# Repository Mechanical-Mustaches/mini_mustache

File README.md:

Temporary home for a browser based serial terminal can be found here https://anfroholic.github.io/stache-terminal/

We are the Mechanical Mustaches
FIRST® Robotics Team 8122

this is Mo the mini_mustache robotic car

Mo Dance for the FIRST Time!

Mo designed by our very own Olivia

Coming soon! Carl the Controller

here is a race put on by our amazing lead progammer Angie!!

Still in development but some previews are:

Mo hosts webpages to edit himself
## Homepage

## Live coding REPL like code terminal

## Stachboard
Dashboard is autopopulated with motors, servos, agents and many other inputs and outputs that are created

## Mo also has an editor where you can edit your own code

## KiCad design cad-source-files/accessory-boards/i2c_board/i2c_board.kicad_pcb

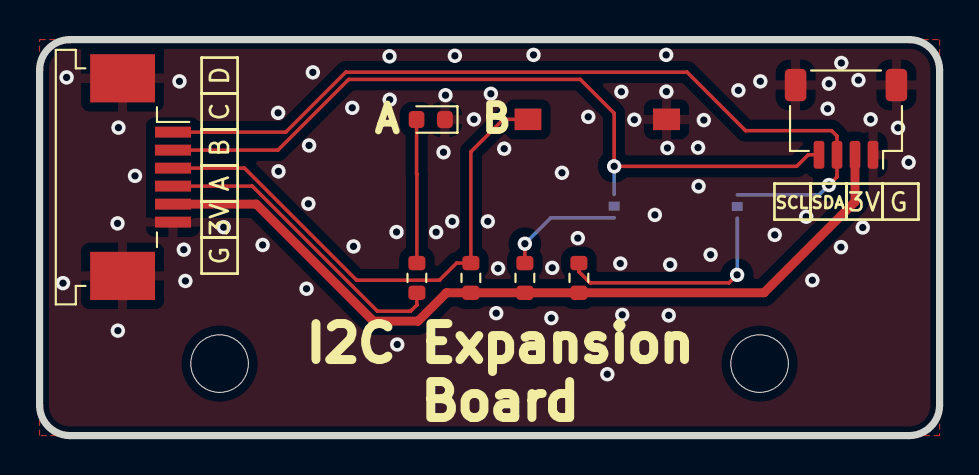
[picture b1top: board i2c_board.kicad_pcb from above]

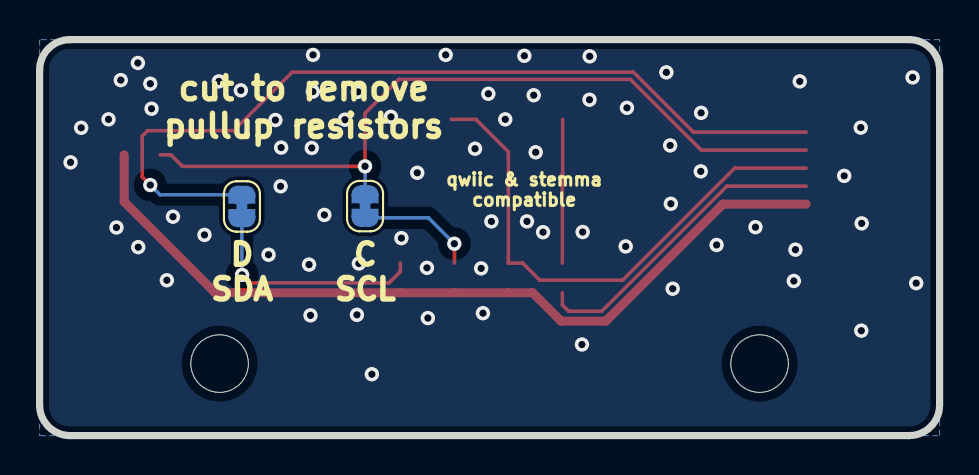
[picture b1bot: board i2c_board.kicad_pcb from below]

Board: 2 copper layers, 50.0 x 22.0 mm, 12 parts (2 on the bottom side), 9 nets.

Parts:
D1: led_g; LED_0603_1608Metric
H1, H2: MountingHole; MountingHole_3.2mm_M3_ISO14580
J1: Conn_01x04_MountingPin; JST_SH_SM04B-SRSS-TB_1x04-1MP_P1.00mm_Horizontal
J9: Conn_01x06_MountingPin; TE_84952-6_1x06-1MP_P1.0mm_Horizontal
JP1, JP2: Jumper_2_Open; SolderJumper-2_P1.3mm_Bridged_RoundedPad1.0x1.5mm
R1, R4: 10k; R_0603_1608Metric
R2, R3: 4.7k; R_0603_1608Metric
SW1: SW_Push; SWITCH_2x3_SMD_TACTILE_GREEN

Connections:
+3V3: J1.2, J9.5, R1.2, R2.2, R3.2
/A: J9.4, R4.1
/B: J9.3, R1.1, SW1.1
/C: J1.4, J9.2, JP1.1 (A)
/D: J1.3, J9.1, JP2.1 (A)
GND: D1.1 (K), J1.1, J1.MP (MountPin), J9.6, J9.MP (MountPin), SW1.2
unnamed: D1.2 (A), R4.2
unnamed: JP1.2 (B), R2.1
unnamed: JP2.2 (B), R3.1

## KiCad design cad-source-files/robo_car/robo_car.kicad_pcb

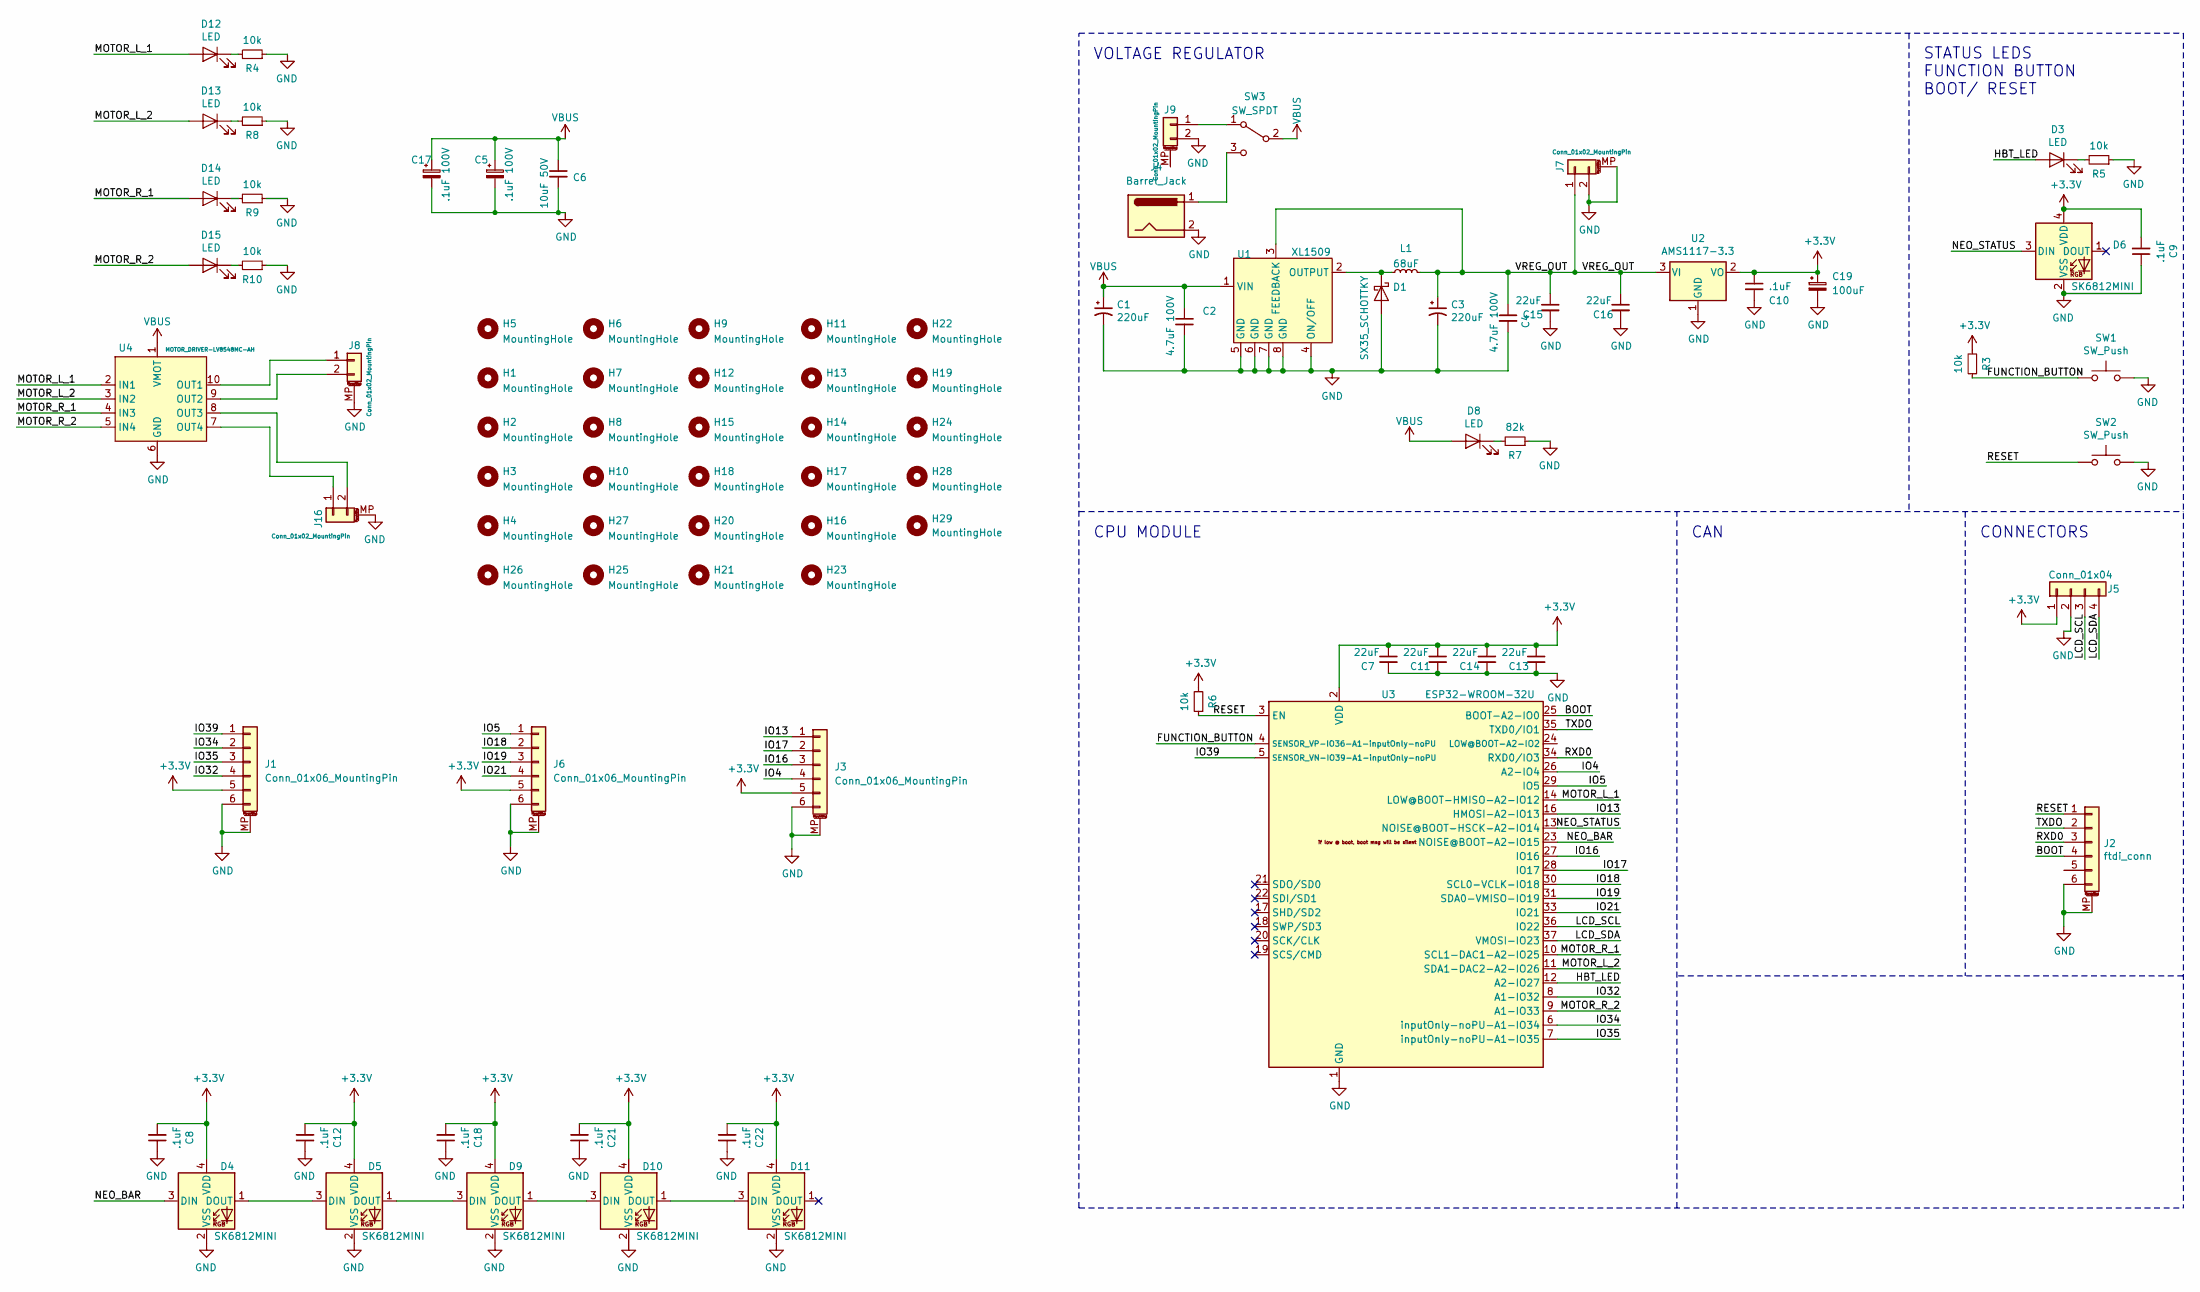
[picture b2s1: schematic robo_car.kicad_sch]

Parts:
C1, C3: 220uF; CP_Elec_10x10.5
C2, C4: 4.7uF 100V; C_0805_2012Metric
C5, C17: .1uF 100V; C_0805_2012Metric
C6: 10uF 50V; C_1206_3216Metric
C7, C11, C13, C14, C15, C16: 22uF; C_0805_2012Metric
C8, C9, C10, C12, C18, C21, C22: .1uF; C_0603_1608Metric
C19: 100uF; CP_EIA-3528-21_Kemet-B
D1: SX35_SCHOTTKY; D_SMA
D3, D8, D12, D13, D14, D15: LED; LED_0603_1608Metric
D4, D5, D6, D9, D10, D11: SK6812MINI; LED_SK6812MINI_PLCC4_3.5x3.5mm_P1.75mm
H1, H2, H3, H4, H5, H6, H7, H8, H9, H10, H11, H12, H13, H14, H15, H16, H17, H18, H19, H20, H25, H26, H27, H28, H29: MountingHole; MountingHole_3.2mm_M3_ISO14580
H21, H22, H23, H24: MountingHole; MountingHole_2.7mm_M2.5_ISO14580
J1, J3, J6: Conn_01x06_MountingPin; TE_84952-6_1x06-1MP_P1.0mm_Horizontal
J2: ftdi_conn; JST_SH_SM06B-SRSS-TB_1x06-1MP_P1.00mm_Horizontal
J4: Barrel_Jack; BarrelJack_Horizontal
J5: Conn_01x04; PinSocket_1x04_P2.54mm_Vertical
J7: Conn_01x02_MountingPin; JST_PH_B2B-PH-K_1x02_P2.00mm_Vertical
J8, J16: Conn_01x02_MountingPin; JST_PH_S2B-PH-K_1x02_P2.00mm_Horizontal
J9: Conn_01x02_MountingPin; JST_XH_B2B-XH-AM_1x02_P2.50mm_Vertical
L1: 68uF; INDUCTOR-68uH
R3, R4, R5, R6, R8, R9, R10: 10k; R_0603_1608Metric
R7: 82k; R_0603_1608Metric
SW1, SW2: SW_Push; SWITCH_2x3_SMD_TACTILE_GREEN
SW3: SW_SPDT; SW_SLIDE_SS-12D10L9
U1: XL1509; SOIC-8_3.9x4.9mm_P1.27mm
U2: AMS1117-3.3; SOT-223-3_TabPin2
U3: ESP32-WROOM-32U; ESP32-WROOM-32U_evezor
U4: MOTOR_DRIVER-LV8548MC-AH; SOIC-10_LV8548MC-AH_evezor

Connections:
+3V3: C7.1, C8.2, C9.2, C10.1, C11.1, C12.2, C13.1, C14.1, C18.2, C19.1, C21.2, C22.2, D4.4 (VDD), D5.4 (VDD), D6.4 (VDD), D9.4 (VDD), D10.4 (VDD), D11.4 (VDD), J1.5, J3.5, J5.1, J6.5, R3.2, R6.2, U2.2 (VO), U3.2 (VDD); also elsewhere on the board
/BOOT: J2.4, U3.25 (BOOT-A2-IO0)
/FUNCTION_BUTTON: R3.1, SW1.1, U3.4 (SENSOR_VP-IO36-A1-inputOnly-noPU)
/HBT_LED: D3.2 (A), U3.12 (A2-IO27)
/IO4: J3.4, U3.26 (A2-IO4)
/IO5: J6.1, U3.29 (IO5)
/IO13: J3.1, U3.16 (HMOSI-A2-IO13)
/IO16: J3.3, U3.27 (IO16)
/IO17: J3.2, U3.28 (IO17)
/IO18: J6.2, U3.30 (SCL0-VCLK-IO18)
/IO19: J6.3, U3.31 (SDA0-VMISO-IO19)
/IO21: J6.4, U3.33 (IO21)
/IO32: J1.4, U3.8 (A1-IO32)
/IO34: J1.2, U3.6 (inputOnly-noPU-A1-IO34)
/IO35: J1.3, U3.7 (inputOnly-noPU-A1-IO35)
/IO39: J1.1, U3.5 (SENSOR_VN-IO39-A1-inputOnly-noPU)
/LCD_SCL: J5.3, U3.36 (IO22)
/LCD_SDA: J5.4, U3.37 (VMOSI-IO23)
/MOTOR_L_1: D12.2 (A), U3.14 (LOW@BOOT-HMISO-A2-IO12), U4.2 (IN1)
/MOTOR_L_2: D13.2 (A), U3.11 (SDA1-DAC2-A2-IO26), U4.3 (IN2)
/MOTOR_R_1: D14.2 (A), U3.10 (SCL1-DAC1-A2-IO25), U4.4 (IN3)
/MOTOR_R_2: D15.2 (A), U3.9 (A1-IO33), U4.5 (IN4)
/NEO_BAR: D4.3 (DIN), U3.23 (NOISE@BOOT-A2-IO15)
/NEO_STATUS: D6.3 (DIN), U3.13 (NOISE@BOOT-HSCK-A2-IO14)
/RESET: J2.1, R6.1, SW2.1, U3.3 (EN)
/RXD0: J2.3, U3.34 (RXD0/IO3)
/TXDO: J2.2, U3.35 (TXD0/IO1)
/VREG_OUT: C3.1, C4.1, C15.1, C16.1, J7.1, L1.1, U1.3 (FEEDBACK), U2.3 (VI)
GND: C1.2, C2.2, C3.2, C4.2, C5.2, C6.2, C7.2, C8.1, C9.1, C10.2, C11.2, C12.1, C13.2, C14.2, C15.2, C16.2, C17.2, C18.1, C19.2, C21.1, C22.1, D1.2 (A), D4.2 (VSS), D5.2 (VSS), D6.2 (VSS), D9.2 (VSS), D10.2 (VSS), D11.2 (VSS), J1.6, J1.MP (MountPin), J2.6, J2.MP (MountPin), J3.6, J3.MP (MountPin), J4.2, J5.2, J6.6, J6.MP (MountPin), J7.2, J7.MP (MountPin), J8.MP (MountPin), J9.2, J16.MP (MountPin), R4.1, R5.1, R7.1, R8.1, R9.1, R10.1, SW1.2, SW2.2, U1.4 (ON/OFF), U1.5 (GND), U1.6 (GND), U1.7 (GND), U1.8 (GND), U2.1 (GND), U3.1 (GND), U3.15 (GND), U3.38 (GND), U3.39 (GND), U4.6 (GND); also elsewhere on the board
unnamed: D1.1 (K), L1.2, U1.2 (OUTPUT)
unnamed: D3.1 (K), R5.2
unnamed: D4.1 (DOUT), D5.3 (DIN)
unnamed: D5.1 (DOUT), D9.3 (DIN)
unnamed: D8.1 (K), R7.2
unnamed: D10.1 (DOUT), D11.3 (DIN)
unnamed: D9.1 (DOUT), D10.3 (DIN)
unnamed: D12.1 (K), R4.2
unnamed: D13.1 (K), R8.2
unnamed: D14.1 (K), R9.2
unnamed: D15.1 (K), R10.2
unnamed: J4.1, SW3.3 (C)
unnamed: J8.1, U4.10 (OUT1)
unnamed: J8.2, U4.9 (OUT2)
unnamed: J16.1, U4.7 (OUT4)
unnamed: J16.2, U4.8 (OUT3)
unnamed: J9.1, SW3.1 (A)
VBUS: C1.1, C2.1, C5.1, C6.1, C17.1, D8.2 (A), SW3.2 (B), U1.1 (VIN), U4.1 (VMOT)

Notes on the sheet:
VOLTAGE REGULATOR
CPU MODULE
CAN
STATUS LEDS FUNCTION BUTTON BOOT/ RESET
CONNECTORS

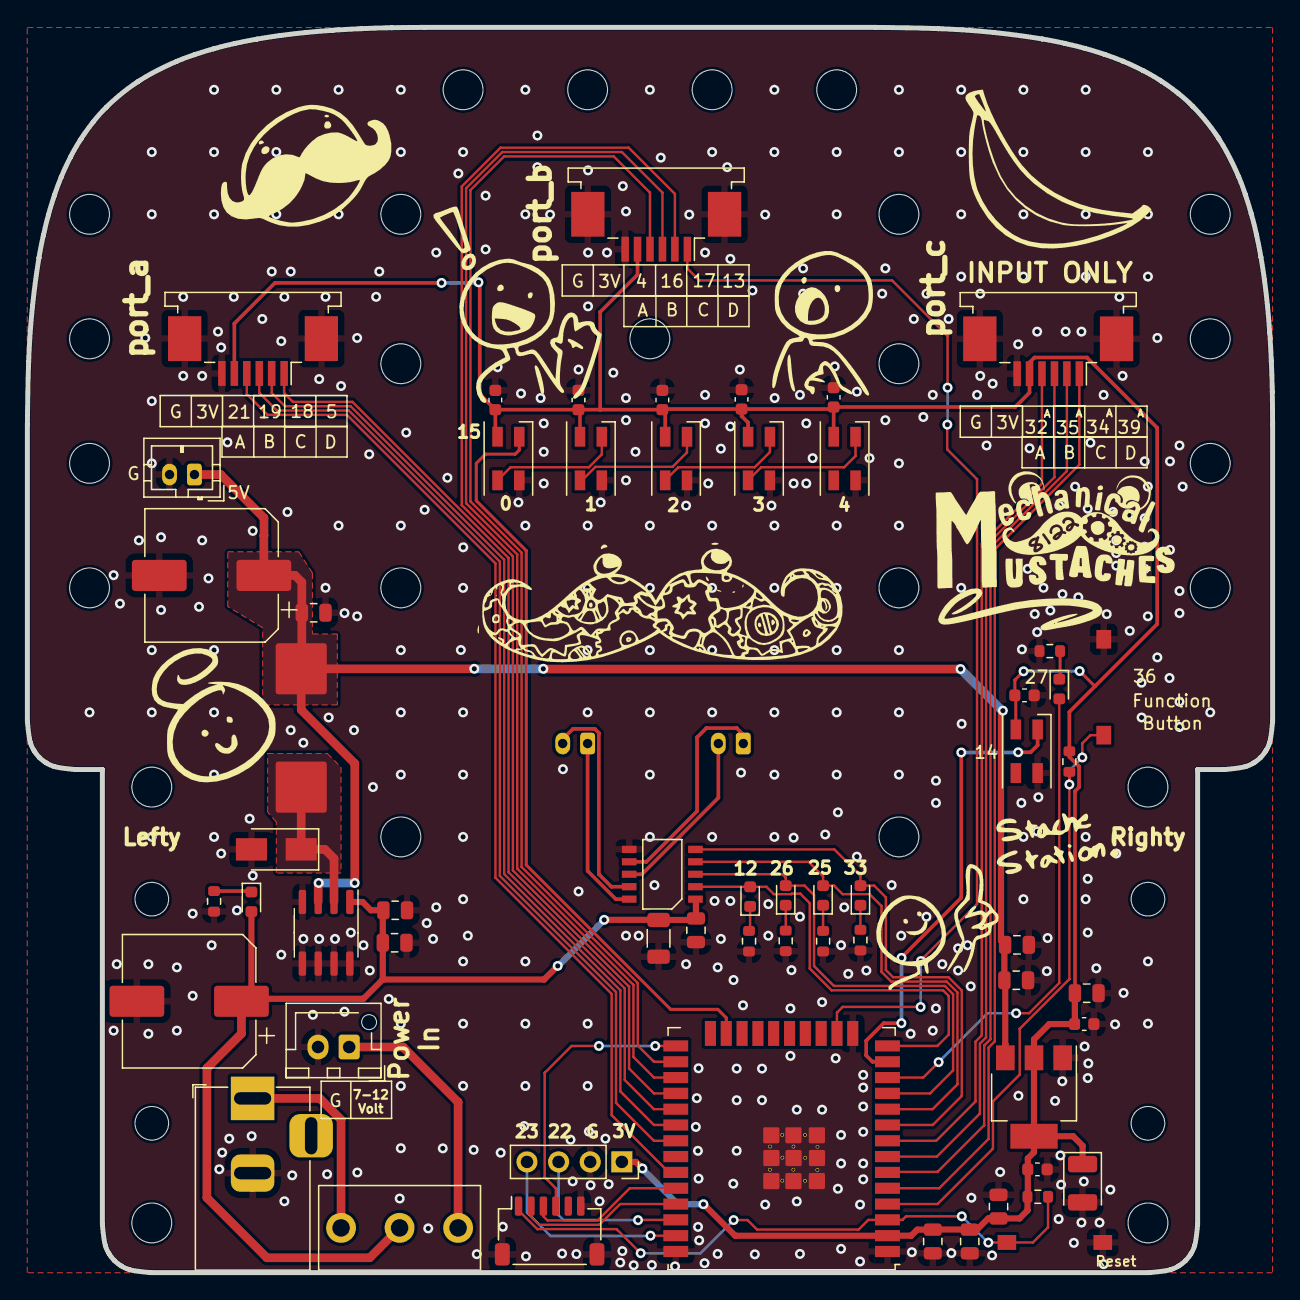
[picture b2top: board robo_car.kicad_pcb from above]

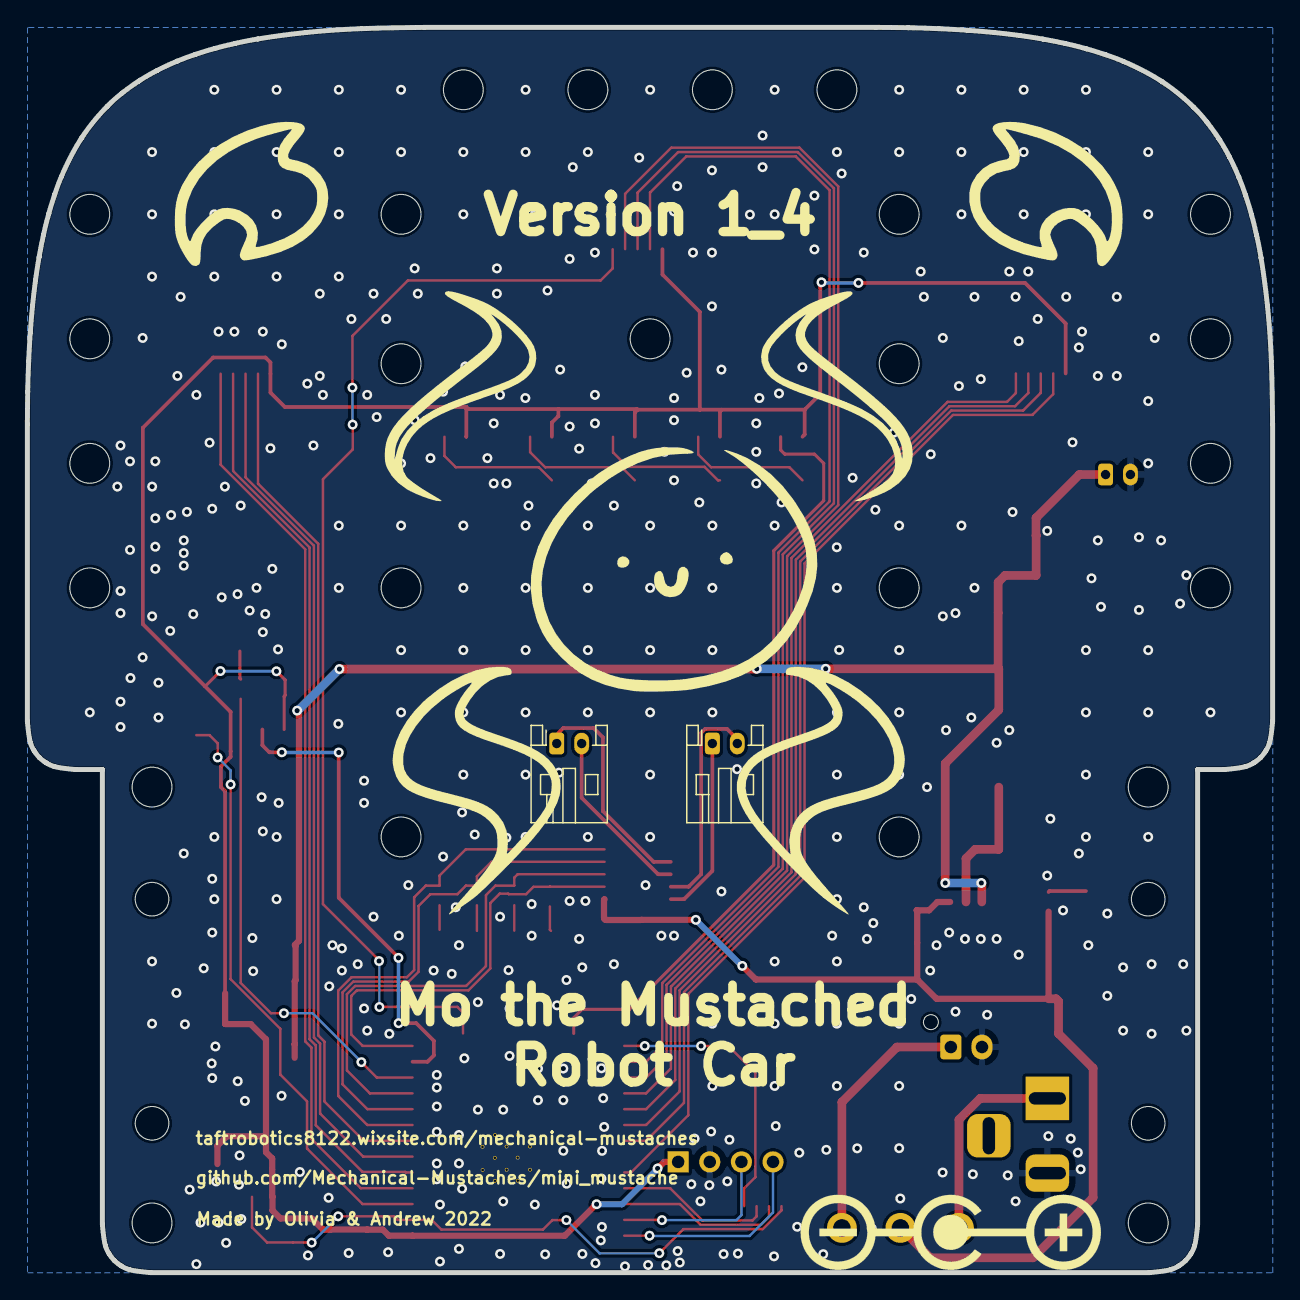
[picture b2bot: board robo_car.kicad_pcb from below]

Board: 2 copper layers, 100.0 x 100.0 mm, 90 parts (2 on the bottom side), 47 nets.

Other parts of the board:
C14#2: .1uF; C_0603_1608Metric

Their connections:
+3V3: C14#2.1; also elsewhere on the board
GND: C14#2.2; also elsewhere on the board

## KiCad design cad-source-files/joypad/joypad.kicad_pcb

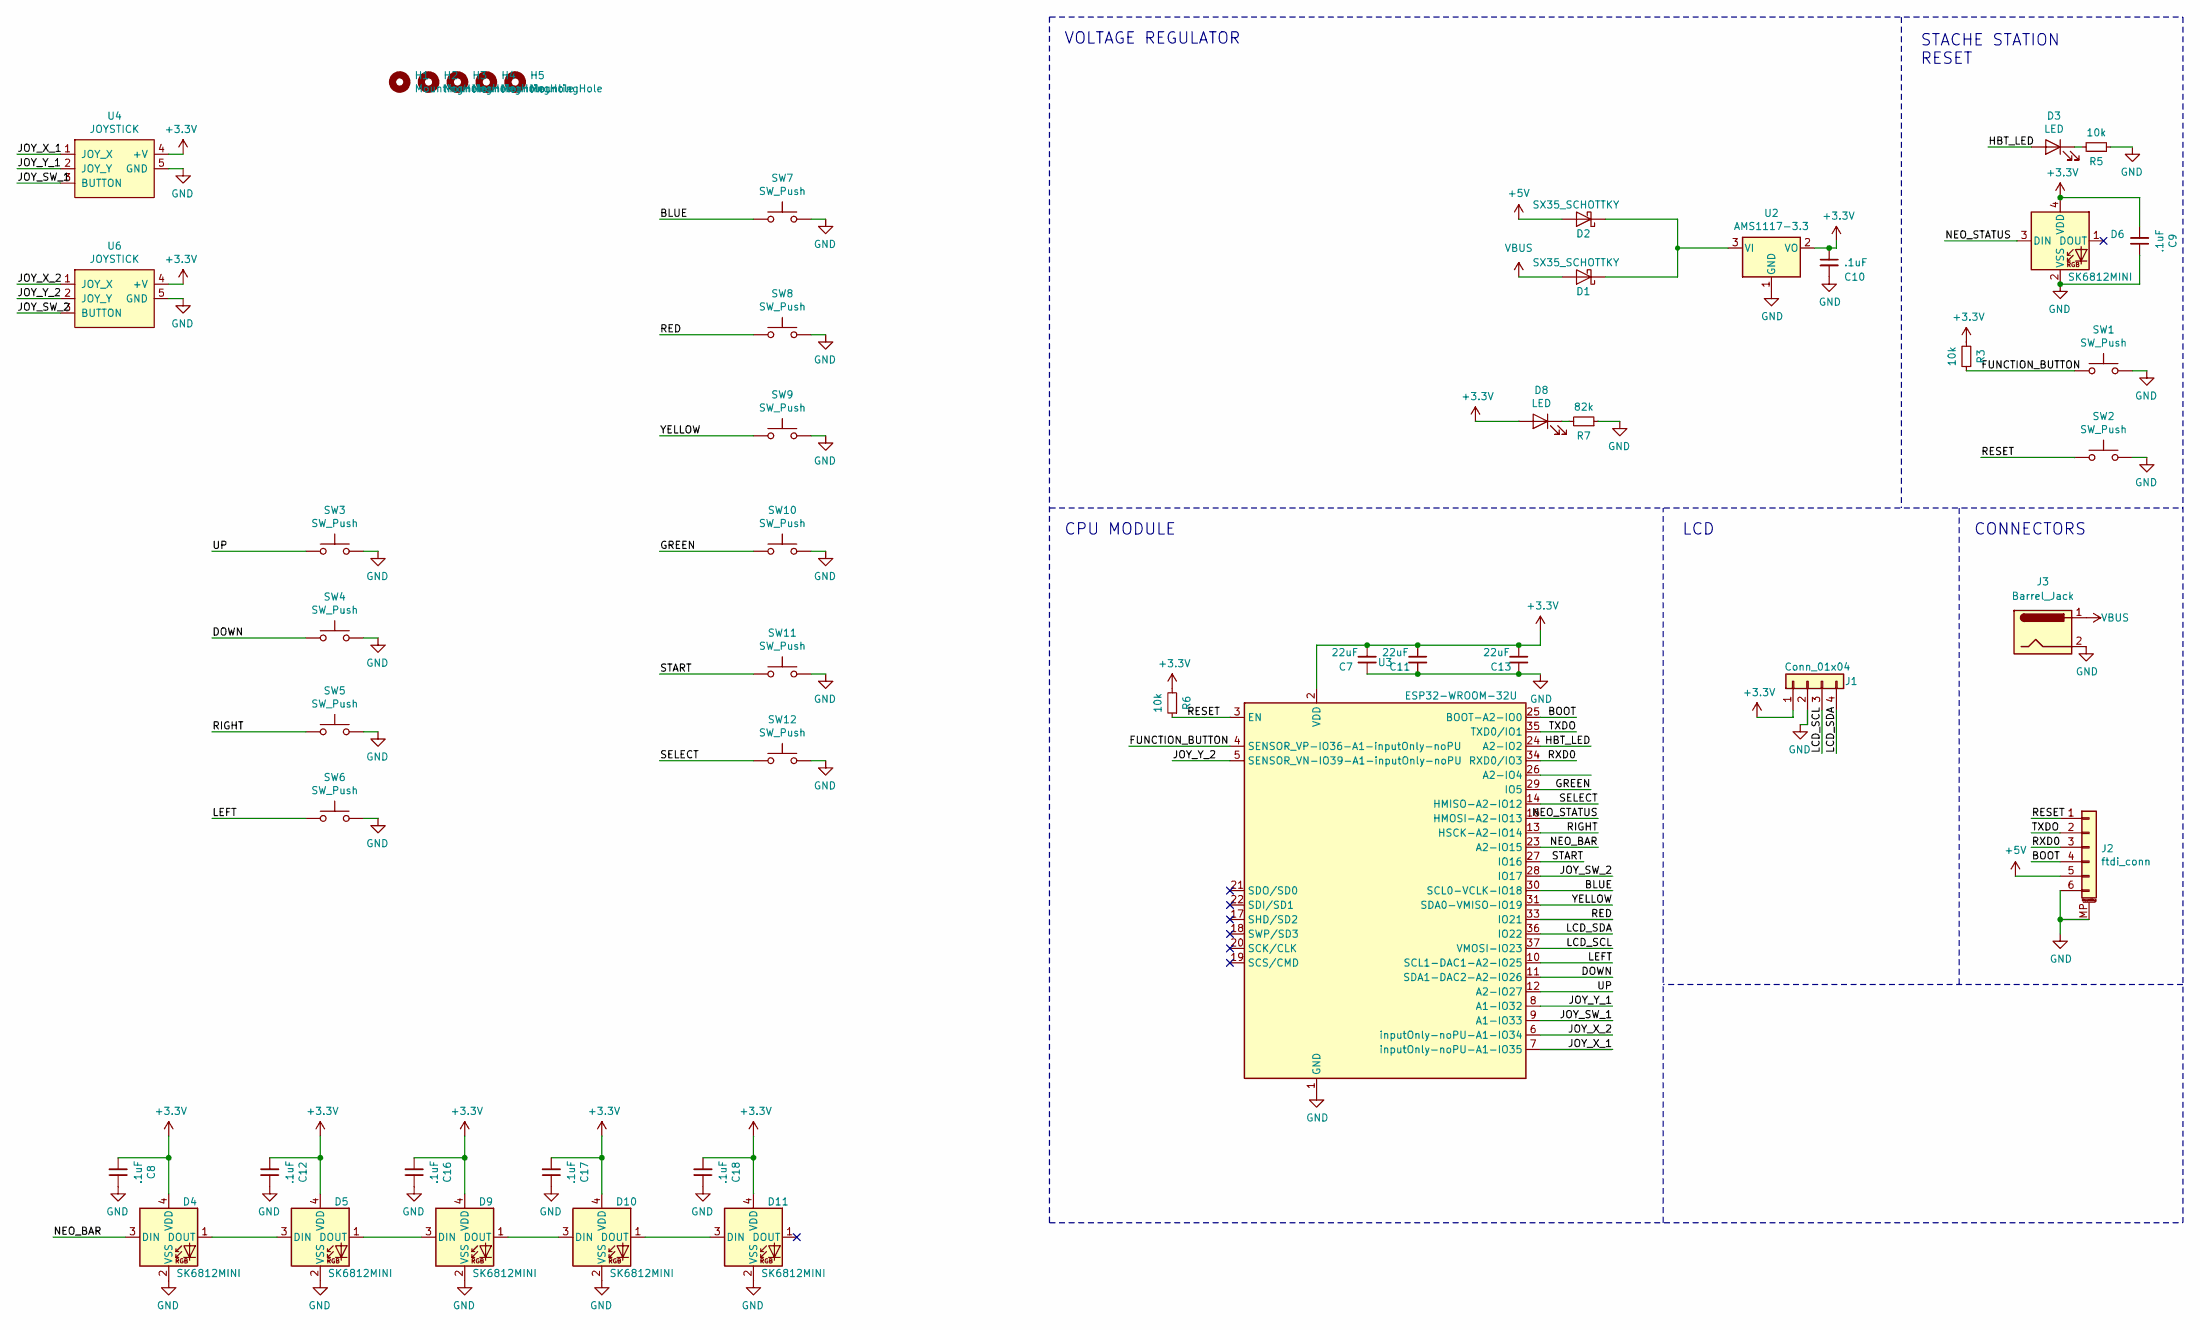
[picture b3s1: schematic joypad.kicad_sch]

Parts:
C7, C11, C13: 22uF; C_0805_2012Metric
C8, C9, C10, C12, C16, C17, C18: .1uF; C_0603_1608Metric
D1, D2: SX35_SCHOTTKY; D_SMA
D3, D8: LED; LED_0603_1608Metric
D4, D5, D6, D9, D10, D11: SK6812MINI; LED_SK6812MINI_PLCC4_3.5x3.5mm_P1.75mm
H1, H2, H3, H4, H5: MountingHole; MountingHole_2.5mm_Pad
J1: Conn_01x04; PinSocket_1x04_P2.54mm_Vertical
J2: ftdi_conn; JST_SH_SM06B-SRSS-TB_1x06-1MP_P1.00mm_Horizontal
J3: Barrel_Jack; BarrelJack_Horizontal
R3, R5, R6: 10k; R_0603_1608Metric
R7: 82k; R_0603_1608Metric
SW1, SW2, SW3, SW4, SW5, SW6, SW11, SW12: SW_Push; SWITCH_2x3_SMD_TACTILE_GREEN
SW7, SW8, SW9, SW10: SW_Push; 12mm_pushbutton
U2: AMS1117-3.3; SOT-223-3_TabPin2
U3: ESP32-WROOM-32U; ESP32-WROOM-32U_evezor
U4, U6: JOYSTICK

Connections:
+3V3: C7.1, C8.2, C9.2, C10.1, C11.1, C12.2, C13.1, C16.2, C17.2, C18.2, D4.4 (VDD), D5.4 (VDD), D6.4 (VDD), D8.2 (A), D9.4 (VDD), D10.4 (VDD), D11.4 (VDD), J1.1, R3.2, R6.2, U2.2 (VO), U3.2 (VDD), U4.4 (+V), U6.4 (+V)
+5V: D2.2 (A), J2.5
/BLUE: SW7.1, U3.30 (SCL0-VCLK-IO18)
/BOOT: J2.4, U3.25 (BOOT-A2-IO0)
/DOWN: SW4.1, U3.11 (SDA1-DAC2-A2-IO26)
/FUNCTION_BUTTON: R3.1, SW1.1, U3.4 (SENSOR_VP-IO36-A1-inputOnly-noPU)
/GREEN: SW10.1, U3.29 (IO5)
/HBT_LED: D3.2 (A), U3.24 (A2-IO2)
/JOY_SW_1: U3.9 (A1-IO33), U4.3 (BUTTON)
/JOY_SW_2: U3.28 (IO17), U6.3 (BUTTON)
/JOY_X_1: U3.7 (inputOnly-noPU-A1-IO35), U4.1 (JOY_X)
/JOY_X_2: U3.6 (inputOnly-noPU-A1-IO34), U6.1 (JOY_X)
/JOY_Y_1: U3.8 (A1-IO32), U4.2 (JOY_Y)
/JOY_Y_2: U3.5 (SENSOR_VN-IO39-A1-inputOnly-noPU), U6.2 (JOY_Y)
/LCD_SCL: J1.3, U3.37 (VMOSI-IO23)
/LCD_SDA: J1.4, U3.36 (IO22)
/LEFT: SW6.1, U3.10 (SCL1-DAC1-A2-IO25)
/NEO_BAR: D4.3 (DIN), U3.23 (A2-IO15)
/NEO_STATUS: D6.3 (DIN), U3.16 (HMOSI-A2-IO13)
/RED: SW8.1, U3.33 (IO21)
/RESET: J2.1, R6.1, SW2.1, U3.3 (EN)
/RIGHT: SW5.1, U3.13 (HSCK-A2-IO14)
/RXD0: J2.3, U3.34 (RXD0/IO3)
/SELECT: SW12.1, U3.14 (HMISO-A2-IO12)
/START: SW11.1, U3.27 (IO16)
/TXDO: J2.2, U3.35 (TXD0/IO1)
/UP: SW3.1, U3.12 (A2-IO27)
/YELLOW: SW9.1, U3.31 (SDA0-VMISO-IO19)
GND: C7.2, C8.1, C9.1, C10.2, C11.2, C12.1, C13.2, C16.1, C17.1, C18.1, D4.2 (VSS), D5.2 (VSS), D6.2 (VSS), D9.2 (VSS), D10.2 (VSS), D11.2 (VSS), J1.2, J2.6, J2.MP (MountPin), J3.2, R5.1, R7.1, SW1.2, SW2.2, SW3.2, SW4.2, SW5.2, SW6.2, SW7.2, SW8.2, SW9.2, SW10.2, SW11.2, SW12.2, U2.1 (GND), U3.1 (GND), U3.15 (GND), U3.38 (GND), U3.39 (GND), U4.5 (GND), U6.5 (GND)
unnamed: D1.1 (K), D2.1 (K), U2.3 (VI)
unnamed: D3.1 (K), R5.2
unnamed: D4.1 (DOUT), D5.3 (DIN)
unnamed: D5.1 (DOUT), D9.3 (DIN)
unnamed: D8.1 (K), R7.2
unnamed: D10.1 (DOUT), D11.3 (DIN)
unnamed: D9.1 (DOUT), D10.3 (DIN)
VBUS: D1.2 (A), J3.1

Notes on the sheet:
VOLTAGE REGULATOR
CPU MODULE
LCD
STACHE STATION RESET
CONNECTORS

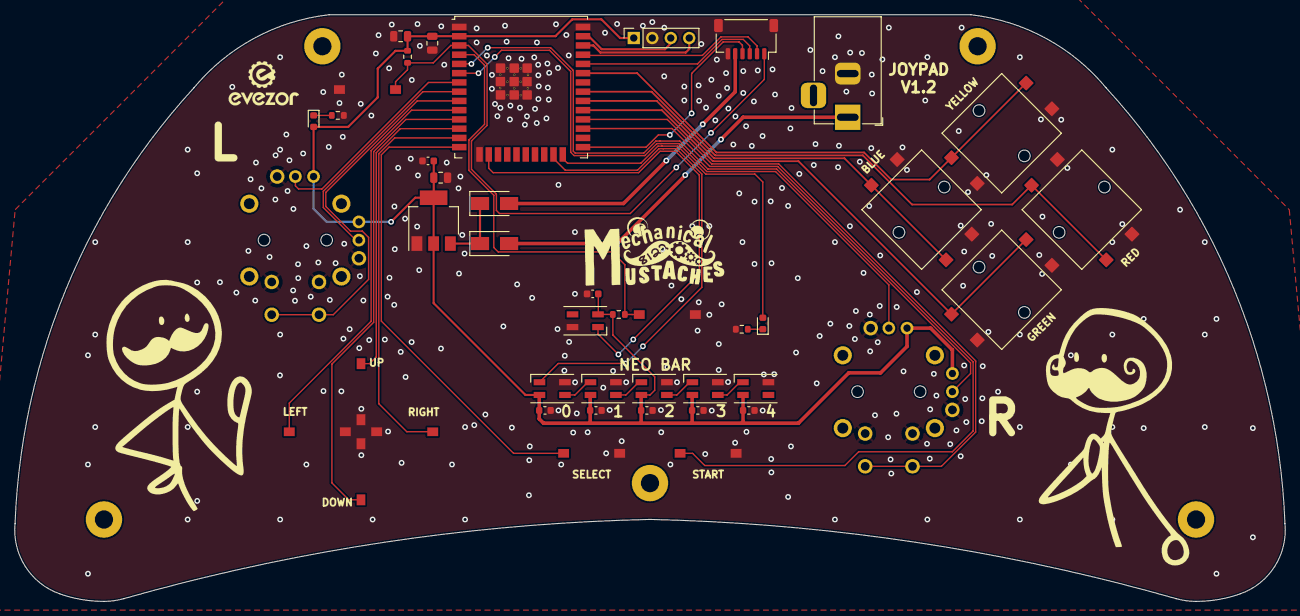
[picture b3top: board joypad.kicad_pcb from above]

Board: 2 copper layers, 174.5 x 80.6 mm, 48 parts (0 on the bottom side), 37 nets.

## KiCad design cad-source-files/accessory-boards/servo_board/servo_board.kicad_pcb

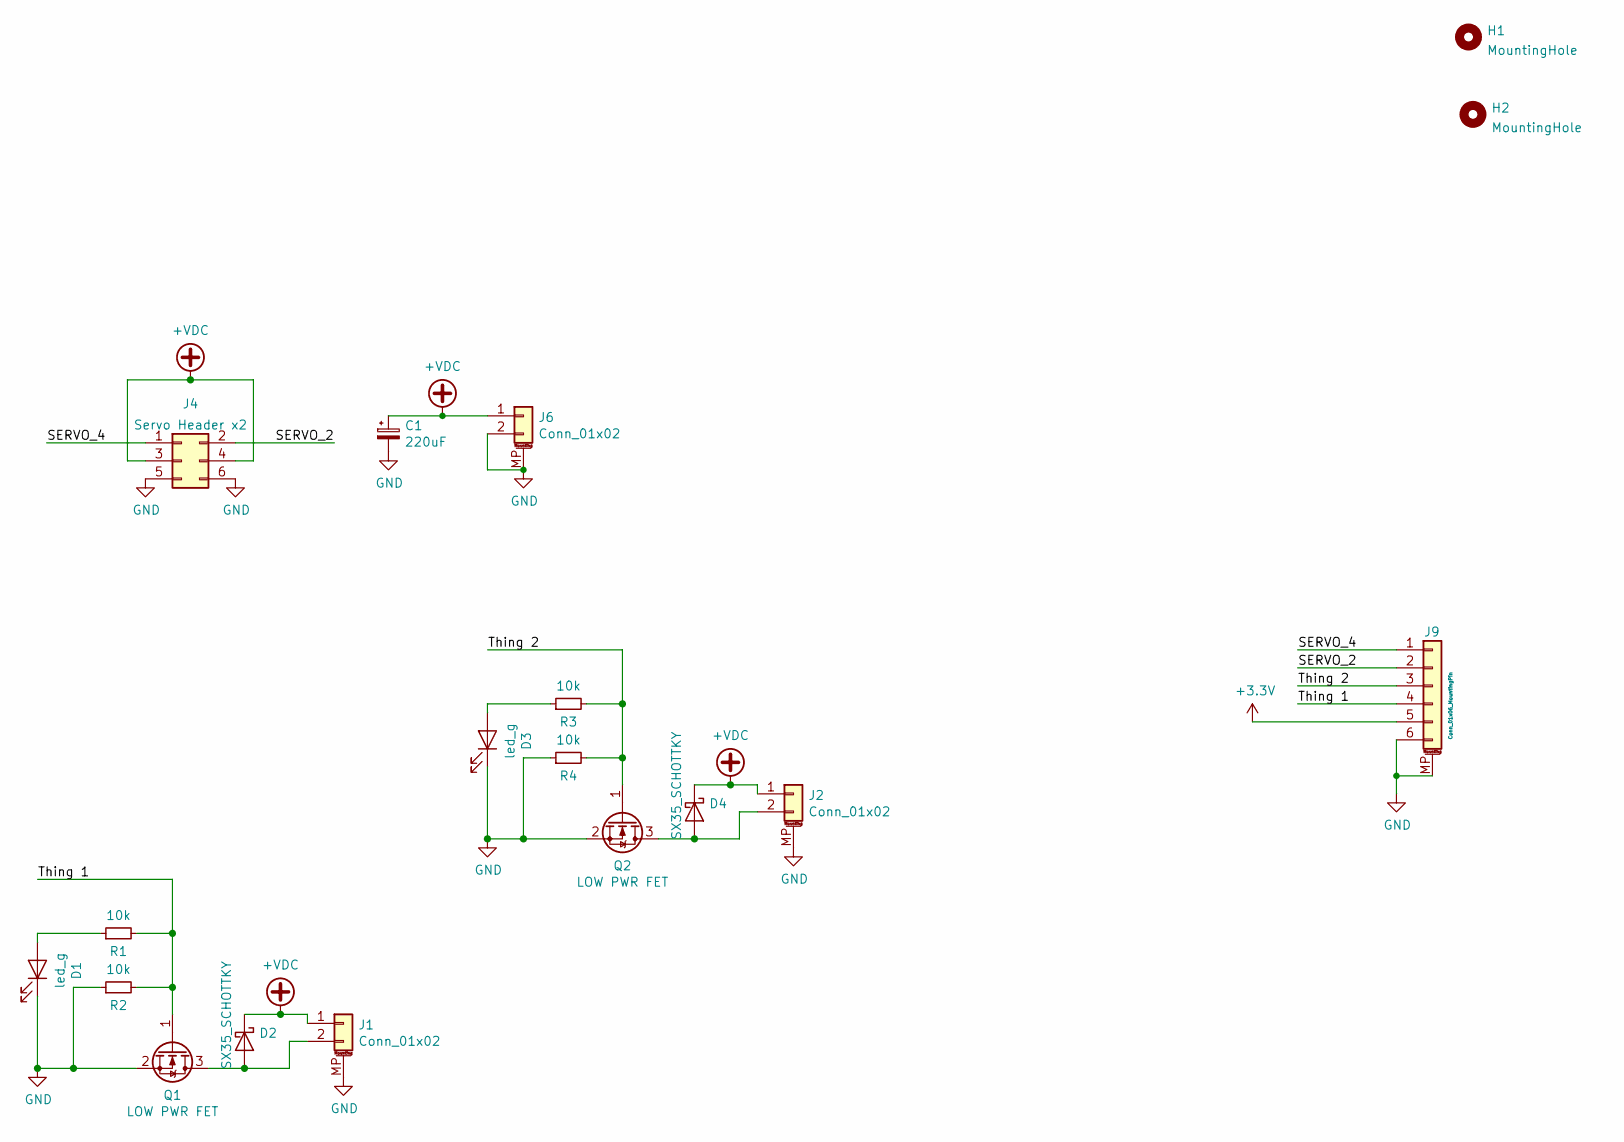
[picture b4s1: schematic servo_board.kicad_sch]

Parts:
C1: 220uF; CP_Elec_8x6.5
D1, D3: led_g; LED_0603_1608Metric
D2, D4: SX35_SCHOTTKY; D_SMA
H1, H2: MountingHole; MountingHole_3.2mm_M3_ISO14580
J1, J2, J6: Conn_01x02; JST_XH_2_VERTICAL
J4: Servo Header x2; PinHeader_2x03_P2.54mm_Vertical_SMD
J9: Conn_01x06_MountingPin; TE_84952-6_1x06-1MP_P1.0mm_Horizontal
Q1, Q2: LOW PWR FET; SOT-23
R1, R2, R3, R4: 10k; R_0603_1608Metric

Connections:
+3V3: J9.5
+VDC: C1.1, D2.1 (K), D4.1 (K), J1.1, J2.1, J4.3, J4.4, J6.1
/SERVO_2: J4.2, J9.2
/SERVO_4: J4.1, J9.1
/Thing 1: J9.4, Q1.1 (G), R1.2, R2.2
/Thing 2: J9.3, Q2.1 (G), R3.2, R4.2
GND: C1.2, D1.1 (K), D3.1 (K), J1.MP (MountPin), J2.MP (MountPin), J4.5, J4.6, J6.2, J6.MP (MountPin), J9.6, J9.MP (MountPin), Q1.2 (S), Q2.2 (S), R2.1, R4.1
unnamed: D1.2 (A), R1.1
unnamed: D2.2 (A), J1.2, Q1.3 (D)
unnamed: D3.2 (A), R3.1
unnamed: D4.2 (A), J2.2, Q2.3 (D)

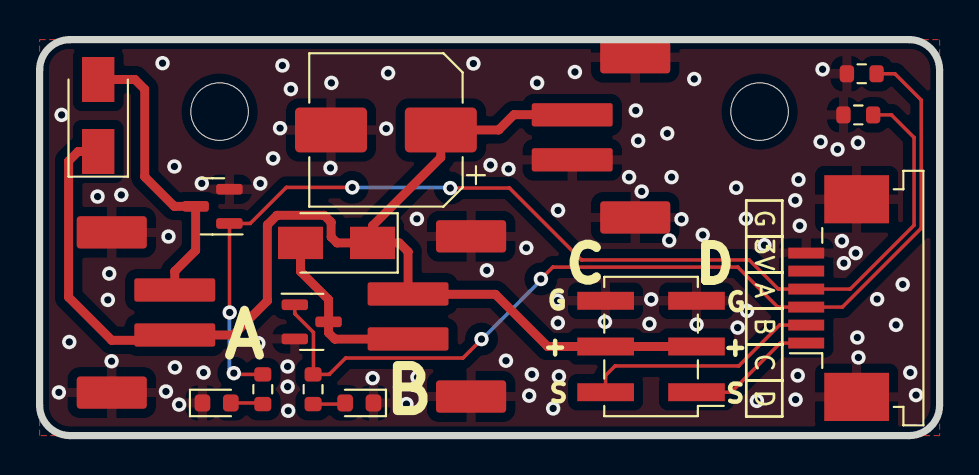
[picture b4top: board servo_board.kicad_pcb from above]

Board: 2 copper layers, 50.0 x 22.0 mm, 18 parts (0 on the bottom side), 10 nets.

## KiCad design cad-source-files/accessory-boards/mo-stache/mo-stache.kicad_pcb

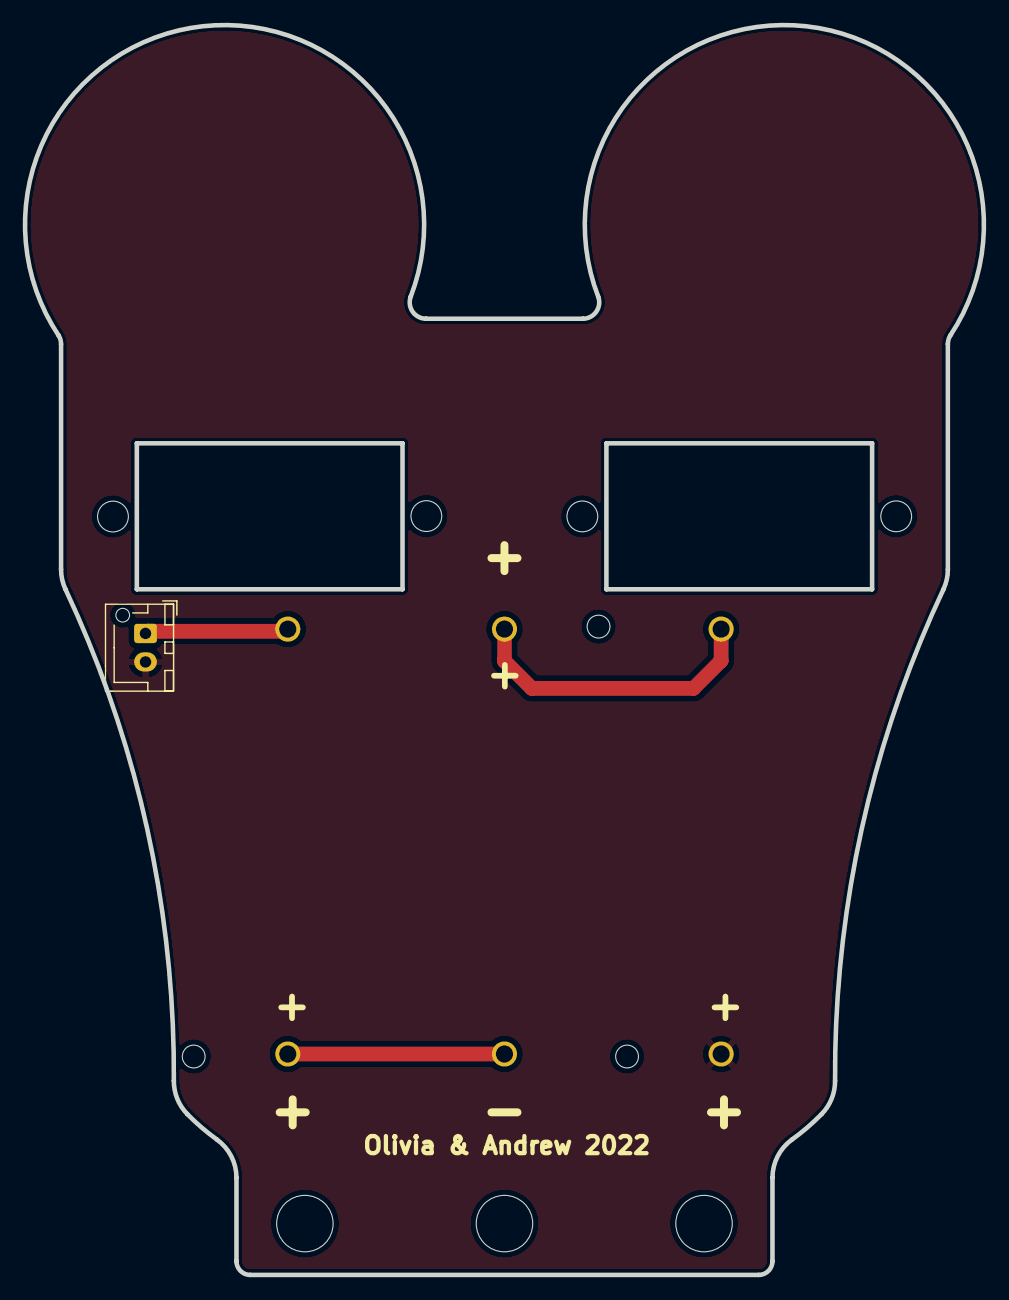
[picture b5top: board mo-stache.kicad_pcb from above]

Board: 2 copper layers, 84.1 x 109.6 mm, 11 parts (0 on the bottom side), 4 nets.

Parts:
BT1, BT2, BT3: Battery_Cell; 16350_holder
H1, H2, H3: MountingHole; MountingHole_4.95mm_3_16in
H4, H5, H6, H7: MountingHole; MountingHole_2.7mm_M2.5_ISO7380
J1: Conn_01x02; JST_XH_B2B-XH-AM_1x02_P2.50mm_Vertical

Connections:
+BATT: BT1.1 (+), J1.1
GND: BT3.2 (-), J1.2
unnamed: BT1.2 (-), BT2.1 (+)
unnamed: BT2.2 (-), BT3.1 (+)

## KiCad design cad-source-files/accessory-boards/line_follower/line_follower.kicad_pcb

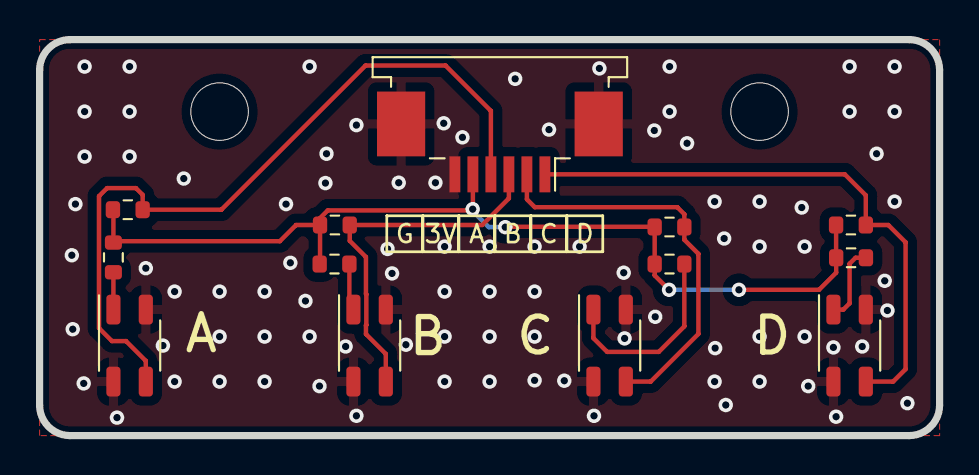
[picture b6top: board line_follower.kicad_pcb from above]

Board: 2 copper layers, 50.0 x 22.0 mm, 15 parts (0 on the bottom side), 10 nets.

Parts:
H1, H2: MountingHole; MountingHole_3.2mm_M3_ISO14580
J9: Conn_01x06_MountingPin; TE_84952-6_1x06-1MP_P1.0mm_Horizontal
R3, R6, R9, R12: R100; R_0603_1608Metric
R5, R8, R10, R13: 10K; R_0603_1608Metric
U1, U2, U3, U4: QRE1113GR; OnSemi_CASE100CY

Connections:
+3V3: J9.5, R3.1, R5.1, R6.1, R8.1, R9.1, R10.1, R12.1, R13.1
/Button A: J9.4, R13.2, U4.3
/Button B: J9.3, R10.2, U3.3
/Button C: J9.2, R5.2, U1.3
/Button D: J9.1, R8.2, U2.3
GND: J9.6, J9.MP (MountPin), U1.2 (K), U1.4, U2.2 (K), U2.4, U3.2 (K), U3.4, U4.2 (K), U4.4
unnamed: R3.2, U1.1 (A)
unnamed: R6.2, U2.1 (A)
unnamed: R9.2, U3.1 (A)
unnamed: R12.2, U4.1 (A)

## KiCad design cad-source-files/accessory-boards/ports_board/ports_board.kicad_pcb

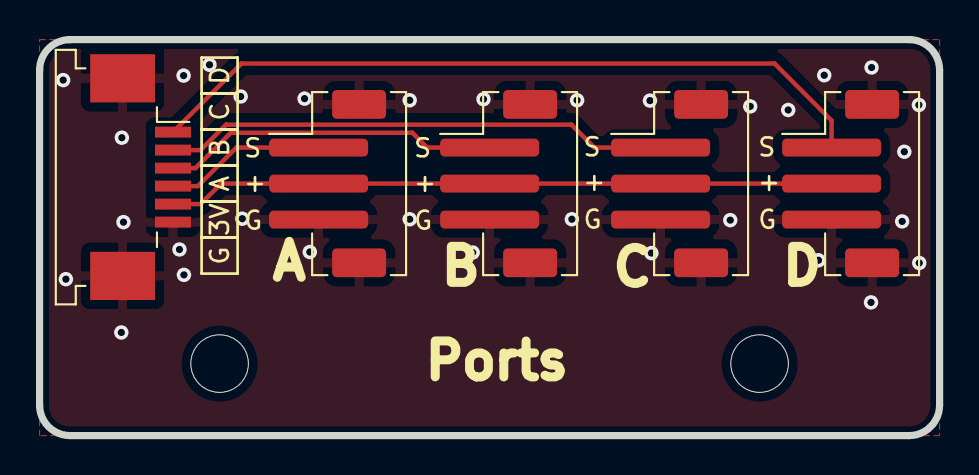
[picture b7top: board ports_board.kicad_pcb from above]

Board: 2 copper layers, 50.0 x 22.0 mm, 7 parts (0 on the bottom side), 6 nets.

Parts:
H1, H2: MountingHole; MountingHole_3.2mm_M3_ISO14580
J2, J5, J7, J8: Conn_01x03; JST_PH_B3B-PH-SM4-TB_1x03-1MP_P2.00mm_Vertical
J9: Conn_01x06_MountingPin; TE_84952-6_1x06-1MP_P1.0mm_Horizontal

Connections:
+3V3: J2.2, J5.2, J7.2, J8.2, J9.5
/A: J2.1, J9.1
/B: J5.1, J9.2
/C: J7.1, J9.3
/D: J8.1, J9.4
GND: J2.3, J2.MP (MountPin), J5.3, J5.MP (MountPin), J7.3, J7.MP (MountPin), J8.3, J8.MP (MountPin), J9.6, J9.MP (MountPin)

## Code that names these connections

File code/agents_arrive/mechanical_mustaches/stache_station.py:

from machine import Pin
from neopixel import NeoPixel
import uasyncio as asyncio

import config

ss = config.stache_station



class StacheStation:
    def __init__(self, hbt_led, function_button, neo_status, **kwargs):
        self.hbt_led = Pin(hbt_led, Pin.OUT)
        self.function_button = Pin(function_button, Pin.IN)
        self.neo = NeoPixel(Pin(neo_status, Pin.OUT), 1)
        self.neo[0] = (0,0,0)
        self.neo.write()


    def check(self):
        if not self.function_button.value():
            print('function button pressed')
            self.neo[0] = (4,12,0)
            self.neo.write()
            raise KeyboardInterrupt
        
    async def hbt(self):
        while True:
            self.hbt_led.value(not self.hbt_led.value())
            await asyncio.sleep_ms(500)
        
    def fill(self, r, g, b):
        self.neo[0] = (r,g,b)
        self.neo.write()
        
    
        

    
